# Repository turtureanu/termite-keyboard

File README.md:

# Termite

> [!IMPORTANT]
> **July 26th was the date I submitted this keyboard for review, today on October 6th I noticed that I forgot to add the firmware (which would have been caught by a reviewer).**

> [!IMPORTANT]
> Made for [Hackboard](https://hackpad.hackclub.com/keyboard), which requires having made a macropad as part of [Hackpad *V2*](https://hackpad.hackclub.com/). \
> Here is my Hackpad V2 macropad: [Wirepad](https://github.com/turtureanu/hackpad/tree/main/hackpads/wirepad)

This is a 34-key ortholinear split keyboard with built-in wrist supports, one 0.91" OLED display on each half, and low-profile mechanical Cherry-MX type switches (Gateron). I use a TRRS cable to connect the two halves. The case is 3D printed and uses 5 M2 screws (four M2x12, one M2x4).

For the firmware I'm using KMK.

I created this keyboard as a replacement for my laptop's keyboard, which might fail soon. I wanted an ortholinear split keyboard with fewer keys that would fit the Engram keyboard layout. In the past I designed a similar keyboard with an 0.42" OLED display under each key (inspired by [PolyKybd Split 72](https://github.com/thpoll83/PolyKybd)), but I lost that design due to an accidental mass file deletion that BTRFS couldn't recover.

## Schematics

| Main Schematic                                    |
| ------------------------------------------------- |
|  |

| Left LEDs                                                          | Right LEDs                                                           |
| ------------------------------------------------------------------ | -------------------------------------------------------------------- |
|  |  |

| Left Switches                                                              | Right Switches                                                               |
| -------------------------------------------------------------------------- | ---------------------------------------------------------------------------- |
|  |  |

## PCB

> The gerber files can be found in `pcb/gerber`

## BOM

| Name                                                                                                   | Sourcing   | Category  | Amount             | Price (total including shipping) |
|--------------------------------------------------------------------------------------------------------|------------|-----------|--------------------|----------------------------------|
| Orpheus Pico                                                                                           | Hack Club  | MCU       | 2                  | $0                               |
| [Gateron Low Profile Switch 2.0 Red](https://www.aliexpress.com/item/1005005385675189.html)            | AliExpress | switches  | 35 (set)           | $15.85                           |
| [Transparent Keycaps with Black Bed](https://www.aliexpress.com/item/1005005984548224.html)            | AliExpress | keycaps   | 40 (4x 10 pcs set) | $17.55                           |
| [SK6812 MINI-E LED](https://www.aliexpress.com/item/1005003056797785.html)                             | AliExpress | misc      | 100 (set)          | $5.13                            |
| [0.91" White OLED Display](https://www.aliexpress.com/item/1005001572699049.html)                      | AliExpress | misc      | 2                  | $3.61                            |
| [1N4148 THT Diode](https://www.aliexpress.com/item/4000142272546.html)                                 | AliExpress | misc      | 100 (set)          | $1.98                            |
| [PJ-320A 3.5mm Female Jack Connector](https://www.aliexpress.com/item/4001161286315.html)              | AliExpress | misc      | 20 (set)           | $2.13                            |
| [M2x4 Hexagon Countersunk Head Screw with Nut](https://www.aliexpress.com/item/1005006883320887.html)  | AliExpress | fasteners | 50 (set)           | $1.75                            |
| [M2x12 Hexagon Countersunk Head Screw with Nut](https://www.aliexpress.com/item/1005006883320887.html) | AliExpress | fasteners | 50 (set)           | $2.46                            |

Switches & keycaps:

- switches: $0.452 per switch
- keycaps: $0.438 per keycap

Fasteners: $4.21 total

Misc:

- LEDs: $0.0513 per LED
- OLED displays: $1.805 per OLED display
- 1N4148 Diodes: 0.0198 per diode
- Jack connector: $0.1065 per jack connector

Misc total: $12.85

JLCPCB cost, if I were to order it myself: $30.04 total (for the entire keyboard, i.e. both halves)

## Credits

- Raspberry Pi Pico model (RPi_Pico_SMD_TH.kicad_mod): https://github.com/ncarandini/KiCad-RP-Pico/
- SK6812-MINI-E (modified): https://github.com/keebio/Keebio-Parts.pretty
- Gateron Switch (SW_Gateron_LowProfile_THT.kicad_mod / modified): https://github.com/siderakb/key-switches.pretty.git
- 0.91 OLED display: https://github.com/gorbachev/KiCad-SSD1306-0.91-OLED-4pin-128x32.pretty/blob/master/SSD1306-0.91-OLED-4pin-128x32.kicad_mod
- Diode (D_DO-35_SOD27_P7.62mm_Horizontal.kicad_mod / modified): https://gitlab.com/kicad/libraries/kicad-footprints/
- PJ-320A 3.5mm 4-pin Jack Connector: https://github.com/nathanhborger/PJ-320A_KiCad_Library
- TRRS-PJ-320A footprint: https://gitlab.com/kicad/libraries/kicad-footprints/

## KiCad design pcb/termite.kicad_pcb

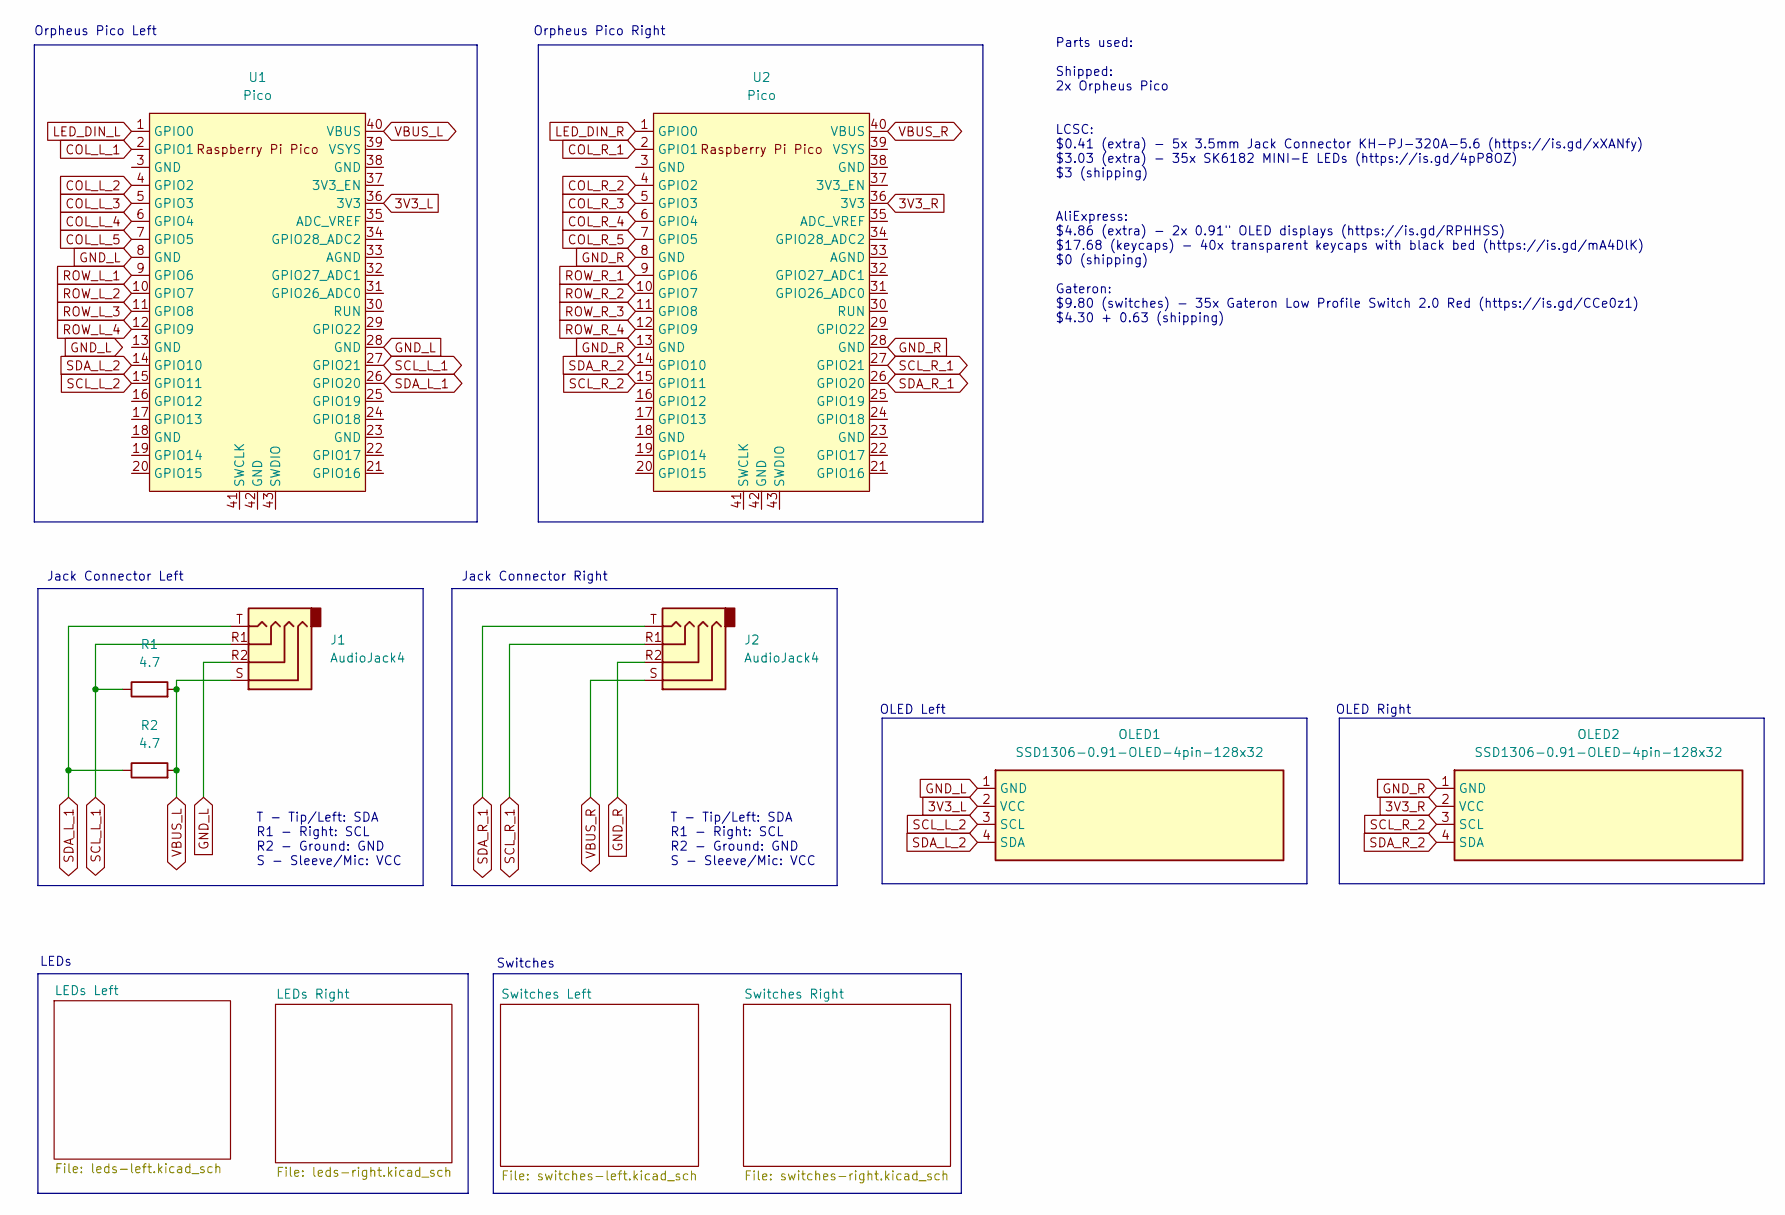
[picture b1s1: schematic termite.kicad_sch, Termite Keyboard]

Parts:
J1, J2: AudioJack4; TRRS-PJ-320A
OLED1, OLED2: SSD1306-0.91-OLED-4pin-128x32
R1, R2: 4.7; R_Axial_DIN0204_L3.6mm_D1.6mm_P5.08mm_Horizontal
U1, U2: Pico; RPi_Pico_SMD_TH

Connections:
3V3_L: OLED1.2 (VCC), U1.36 (3V3)
3V3_R: OLED2.2 (VCC), U2.36 (3V3)
COL_L_1: U1.2 (GPIO1); also elsewhere on the board
COL_L_2: U1.4 (GPIO2); also elsewhere on the board
COL_L_3: U1.5 (GPIO3); also elsewhere on the board
COL_L_4: U1.6 (GPIO4); also elsewhere on the board
COL_L_5: U1.7 (GPIO5); also elsewhere on the board
COL_R_1: U2.2 (GPIO1); also elsewhere on the board
COL_R_2: U2.4 (GPIO2); also elsewhere on the board
COL_R_3: U2.5 (GPIO3); also elsewhere on the board
COL_R_4: U2.6 (GPIO4); also elsewhere on the board
COL_R_5: U2.7 (GPIO5); also elsewhere on the board
GND_L: J1.R2, OLED1.1 (GND), U1.8 (GND), U1.28 (GND); also elsewhere on the board
GND_R: J2.R2, OLED2.1 (GND), U2.8 (GND), U2.13 (GND), U2.28 (GND); also elsewhere on the board
LED_DIN_L: U1.1 (GPIO0); also elsewhere on the board
LED_DIN_R: U2.1 (GPIO0); also elsewhere on the board
ROW_L_1: U1.9 (GPIO6); also elsewhere on the board
ROW_L_2: U1.10 (GPIO7); also elsewhere on the board
ROW_L_3: U1.11 (GPIO8); also elsewhere on the board
ROW_L_4: U1.12 (GPIO9); also elsewhere on the board
ROW_R_1: U2.9 (GPIO6); also elsewhere on the board
ROW_R_2: U2.10 (GPIO7); also elsewhere on the board
ROW_R_3: U2.11 (GPIO8); also elsewhere on the board
ROW_R_4: U2.12 (GPIO9); also elsewhere on the board
SCL_L_1: J1.R1, R1.1, U1.27 (GPIO21)
SCL_L_2: OLED1.3 (SCL), U1.15 (GPIO11)
SCL_R_1: J2.R1, U2.27 (GPIO21)
SCL_R_2: OLED2.3 (SCL), U2.15 (GPIO11)
SDA_L_1: J1.T, R2.1, U1.26 (GPIO20)
SDA_L_2: OLED1.4 (SDA), U1.14 (GPIO10)
SDA_R_1: J2.T, U2.26 (GPIO20)
SDA_R_2: OLED2.4 (SDA), U2.14 (GPIO10)
VBUS_L: J1.S, R1.2, R2.2, U1.40 (VBUS); also elsewhere on the board
VBUS_R: J2.S, U2.40 (VBUS); also elsewhere on the board

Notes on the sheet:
OLED Right
LEDs
T - Tip/Left: SDA R1 - Right: SCL R2 - Ground: GND S - Sleeve/Mic: VCC
Jack Connector Right
Orpheus Pico Right
OLED Left
Parts used: Shipped: 2x Orpheus Pico LCSC: $0.41 (extra) - 5x 3.5mm Jack Connector KH-PJ-320A-5.6 (https://is.gd/xXANfy) $3.03 (extra) - 35x SK6182 MINI-E LEDs (https://is.gd/4pP8OZ) $3 (shipping) AliExpress: $4.86 (extra) - 2x 0.91" OLED displays (https://is.gd/RPHHSS) $17.68 (keycaps) - 40x trans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
Jack Connector Left
Switches
Orpheus Pico Left

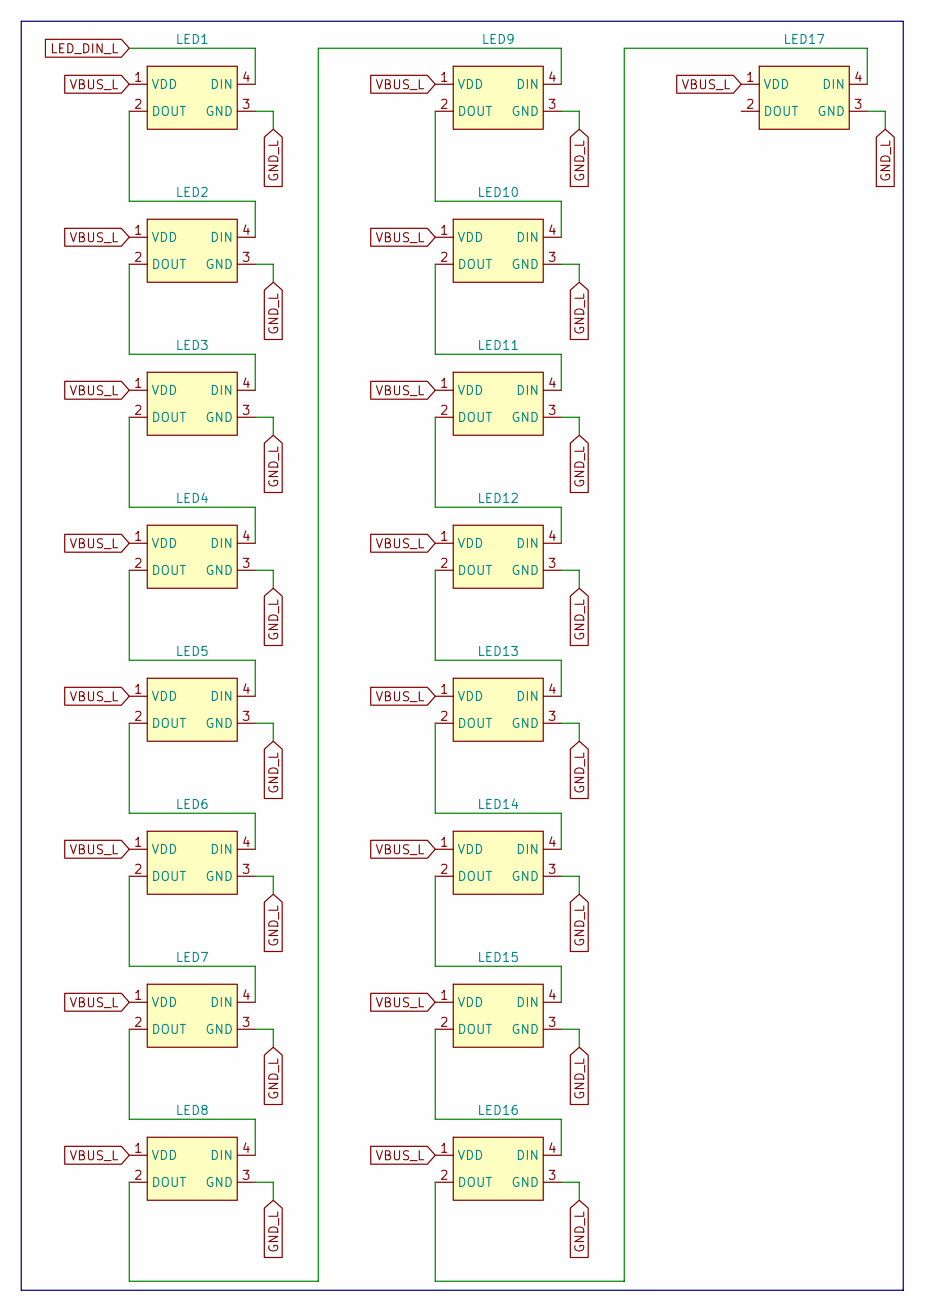
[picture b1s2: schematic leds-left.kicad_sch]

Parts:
LED1, LED2, LED3, LED4, LED5, LED6, LED7, LED8, LED9, LED10, LED11, LED12, LED13, LED14, LED15, LED16, LED17: SK6812-MINI-E

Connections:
GND_L: LED1.3 (GND), LED2.3 (GND), LED3.3 (GND), LED4.3 (GND), LED5.3 (GND), LED6.3 (GND), LED7.3 (GND), LED8.3 (GND), LED9.3 (GND), LED10.3 (GND), LED11.3 (GND), LED12.3 (GND), LED13.3 (GND), LED14.3 (GND), LED15.3 (GND), LED16.3 (GND), LED17.3 (GND); also elsewhere on the board
LED_DIN_L: LED1.4 (DIN); also elsewhere on the board
unnamed: LED1.2 (DOUT), LED2.4 (DIN)
unnamed: LED2.2 (DOUT), LED3.4 (DIN)
unnamed: LED3.2 (DOUT), LED4.4 (DIN)
unnamed: LED4.2 (DOUT), LED5.4 (DIN)
unnamed: LED5.2 (DOUT), LED6.4 (DIN)
unnamed: LED6.2 (DOUT), LED7.4 (DIN)
unnamed: LED7.2 (DOUT), LED8.4 (DIN)
unnamed: LED8.2 (DOUT), LED9.4 (DIN)
unnamed: LED9.2 (DOUT), LED10.4 (DIN)
unnamed: LED10.2 (DOUT), LED11.4 (DIN)
unnamed: LED11.2 (DOUT), LED12.4 (DIN)
unnamed: LED12.2 (DOUT), LED13.4 (DIN)
unnamed: LED13.2 (DOUT), LED14.4 (DIN)
unnamed: LED14.2 (DOUT), LED15.4 (DIN)
unnamed: LED15.2 (DOUT), LED16.4 (DIN)
unnamed: LED16.2 (DOUT), LED17.4 (DIN)
VBUS_L: LED1.1 (VDD), LED2.1 (VDD), LED3.1 (VDD), LED4.1 (VDD), LED5.1 (VDD), LED6.1 (VDD), LED7.1 (VDD), LED8.1 (VDD), LED9.1 (VDD), LED10.1 (VDD), LED11.1 (VDD), LED12.1 (VDD), LED13.1 (VDD), LED14.1 (VDD), LED15.1 (VDD), LED16.1 (VDD), LED17.1 (VDD); also elsewhere on the board

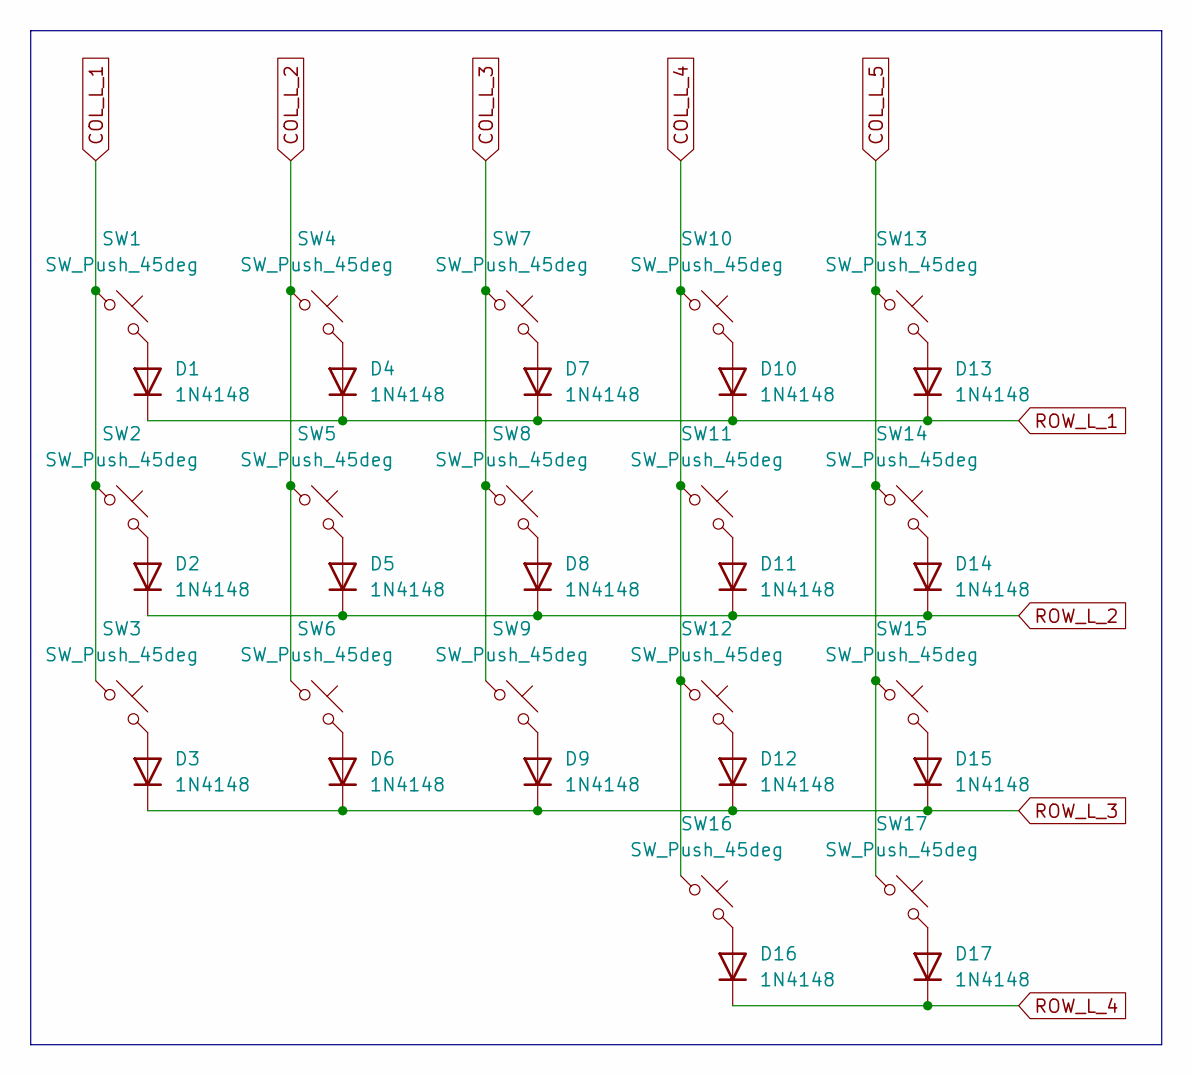
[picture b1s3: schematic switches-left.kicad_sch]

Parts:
D1, D2, D3, D4, D5, D6, D7, D8, D9, D10, D11, D12, D13, D14, D15, D16, D17: 1N4148; D_DO-35_SOD27_P7.62mm_Horizontal
SW1, SW2, SW3, SW4, SW5, SW6, SW7, SW8, SW9, SW10, SW11, SW12, SW13, SW14, SW15, SW16, SW17: SW_Push_45deg; SW_Gateron_LowProfile_THT

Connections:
COL_L_1: SW1.1, SW2.1, SW3.1; also elsewhere on the board
COL_L_2: SW4.1, SW5.1, SW6.1; also elsewhere on the board
COL_L_3: SW7.1, SW8.1, SW9.1; also elsewhere on the board
COL_L_4: SW10.1, SW11.1, SW12.1, SW16.1; also elsewhere on the board
COL_L_5: SW13.1, SW14.1, SW15.1, SW17.1; also elsewhere on the board
unnamed: D1.2 (A), SW1.2
unnamed: D2.2 (A), SW2.2
unnamed: D3.2 (A), SW3.2
unnamed: D4.2 (A), SW4.2
unnamed: D5.2 (A), SW5.2
unnamed: D6.2 (A), SW6.2
unnamed: D7.2 (A), SW7.2
unnamed: D8.2 (A), SW8.2
unnamed: D9.2 (A), SW9.2
unnamed: D10.2 (A), SW10.2
unnamed: D11.2 (A), SW11.2
unnamed: D12.2 (A), SW12.2
unnamed: D13.2 (A), SW13.2
unnamed: D14.2 (A), SW14.2
unnamed: D15.2 (A), SW15.2
unnamed: D16.2 (A), SW16.2
unnamed: D17.2 (A), SW17.2
ROW_L_1: D1.1 (K), D4.1 (K), D7.1 (K), D10.1 (K), D13.1 (K); also elsewhere on the board
ROW_L_2: D2.1 (K), D5.1 (K), D8.1 (K), D11.1 (K), D14.1 (K); also elsewhere on the board
ROW_L_3: D3.1 (K), D6.1 (K), D9.1 (K), D12.1 (K), D15.1 (K); also elsewhere on the board
ROW_L_4: D16.1 (K), D17.1 (K); also elsewhere on the board

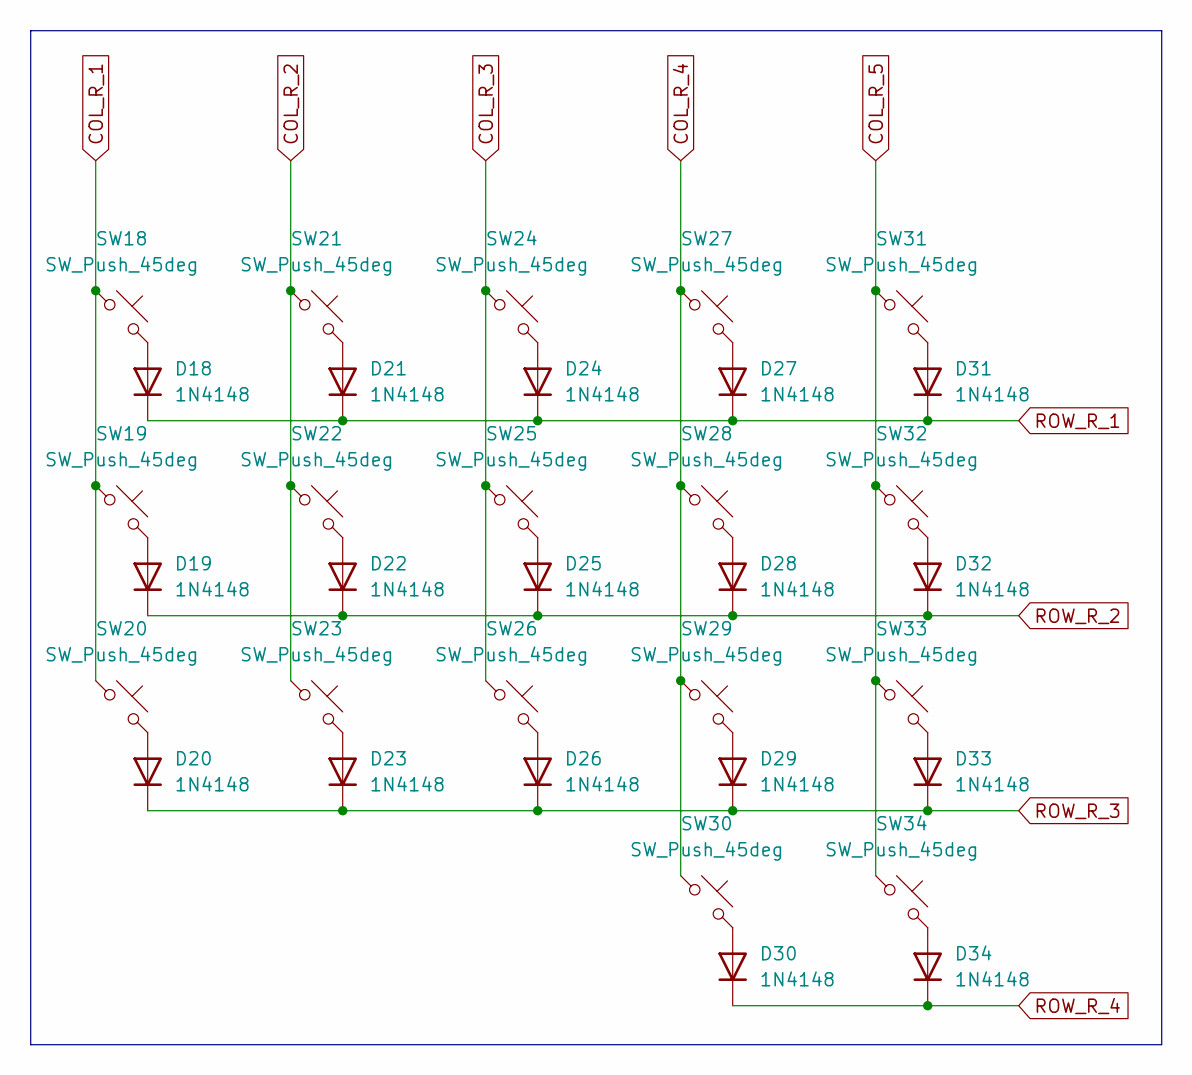
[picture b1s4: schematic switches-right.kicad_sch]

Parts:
D18, D19, D20, D21, D22, D23, D24, D25, D26, D27, D28, D29, D30, D31, D32, D33, D34: 1N4148; D_DO-35_SOD27_P7.62mm_Horizontal
SW18, SW19, SW20, SW21, SW22, SW23, SW24, SW25, SW26, SW27, SW28, SW29, SW30, SW31, SW32, SW33, SW34: SW_Push_45deg; SW_Gateron_LowProfile_THT

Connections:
COL_R_1: SW18.1, SW19.1, SW20.1; also elsewhere on the board
COL_R_2: SW21.1, SW22.1, SW23.1; also elsewhere on the board
COL_R_3: SW24.1, SW25.1, SW26.1; also elsewhere on the board
COL_R_4: SW27.1, SW28.1, SW29.1, SW30.1; also elsewhere on the board
COL_R_5: SW31.1, SW32.1, SW33.1, SW34.1; also elsewhere on the board
unnamed: D18.2 (A), SW18.2
unnamed: D19.2 (A), SW19.2
unnamed: D20.2 (A), SW20.2
unnamed: D21.2 (A), SW21.2
unnamed: D22.2 (A), SW22.2
unnamed: D23.2 (A), SW23.2
unnamed: D24.2 (A), SW24.2
unnamed: D25.2 (A), SW25.2
unnamed: D26.2 (A), SW26.2
unnamed: D27.2 (A), SW27.2
unnamed: D28.2 (A), SW28.2
unnamed: D29.2 (A), SW29.2
unnamed: D30.2 (A), SW30.2
unnamed: D31.2 (A), SW31.2
unnamed: D32.2 (A), SW32.2
unnamed: D33.2 (A), SW33.2
unnamed: D34.2 (A), SW34.2
ROW_R_1: D18.1 (K), D21.1 (K), D24.1 (K), D27.1 (K), D31.1 (K); also elsewhere on the board
ROW_R_2: D19.1 (K), D22.1 (K), D25.1 (K), D28.1 (K), D32.1 (K); also elsewhere on the board
ROW_R_3: D20.1 (K), D23.1 (K), D26.1 (K), D29.1 (K), D33.1 (K); also elsewhere on the board
ROW_R_4: D30.1 (K), D34.1 (K); also elsewhere on the board

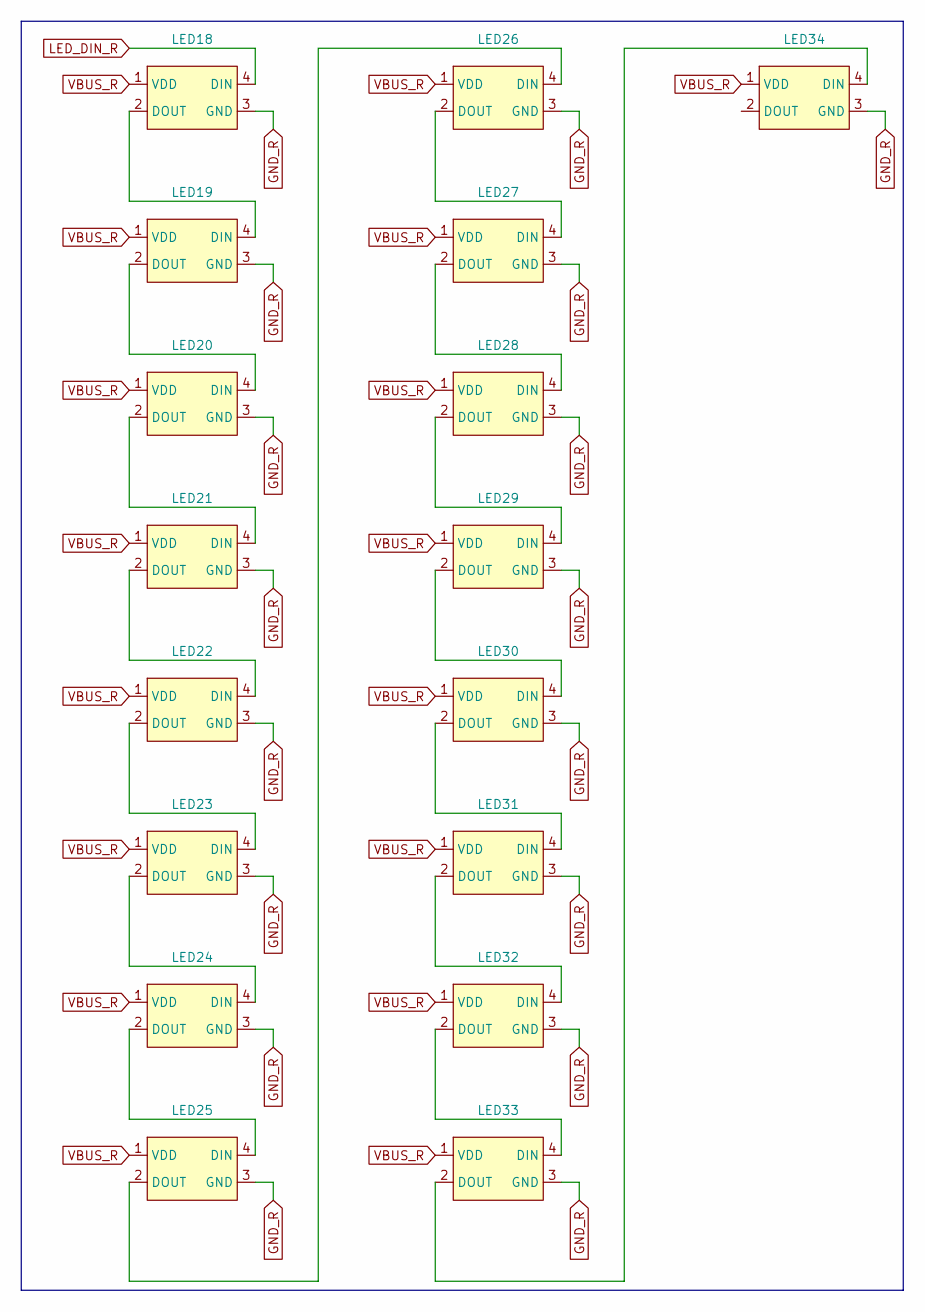
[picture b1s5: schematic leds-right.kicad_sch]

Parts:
LED18, LED19, LED20, LED21, LED22, LED23, LED24, LED25, LED26, LED27, LED28, LED29, LED30, LED31, LED32, LED33, LED34: SK6812-MINI-E

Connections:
GND_R: LED18.3 (GND), LED19.3 (GND), LED20.3 (GND), LED21.3 (GND), LED22.3 (GND), LED23.3 (GND), LED24.3 (GND), LED25.3 (GND), LED26.3 (GND), LED27.3 (GND), LED28.3 (GND), LED29.3 (GND), LED30.3 (GND), LED31.3 (GND), LED32.3 (GND), LED33.3 (GND), LED34.3 (GND); also elsewhere on the board
LED_DIN_R: LED18.4 (DIN); also elsewhere on the board
unnamed: LED18.2 (DOUT), LED19.4 (DIN)
unnamed: LED19.2 (DOUT), LED20.4 (DIN)
unnamed: LED20.2 (DOUT), LED21.4 (DIN)
unnamed: LED21.2 (DOUT), LED22.4 (DIN)
unnamed: LED22.2 (DOUT), LED23.4 (DIN)
unnamed: LED23.2 (DOUT), LED24.4 (DIN)
unnamed: LED24.2 (DOUT), LED25.4 (DIN)
unnamed: LED25.2 (DOUT), LED26.4 (DIN)
unnamed: LED26.2 (DOUT), LED27.4 (DIN)
unnamed: LED27.2 (DOUT), LED28.4 (DIN)
unnamed: LED28.2 (DOUT), LED29.4 (DIN)
unnamed: LED29.2 (DOUT), LED30.4 (DIN)
unnamed: LED30.2 (DOUT), LED31.4 (DIN)
unnamed: LED31.2 (DOUT), LED32.4 (DIN)
unnamed: LED32.2 (DOUT), LED33.4 (DIN)
unnamed: LED33.2 (DOUT), LED34.4 (DIN)
VBUS_R: LED18.1 (VDD), LED19.1 (VDD), LED20.1 (VDD), LED21.1 (VDD), LED22.1 (VDD), LED23.1 (VDD), LED24.1 (VDD), LED25.1 (VDD), LED26.1 (VDD), LED27.1 (VDD), LED28.1 (VDD), LED29.1 (VDD), LED30.1 (VDD), LED31.1 (VDD), LED32.1 (VDD), LED33.1 (VDD), LED34.1 (VDD); also elsewhere on the board

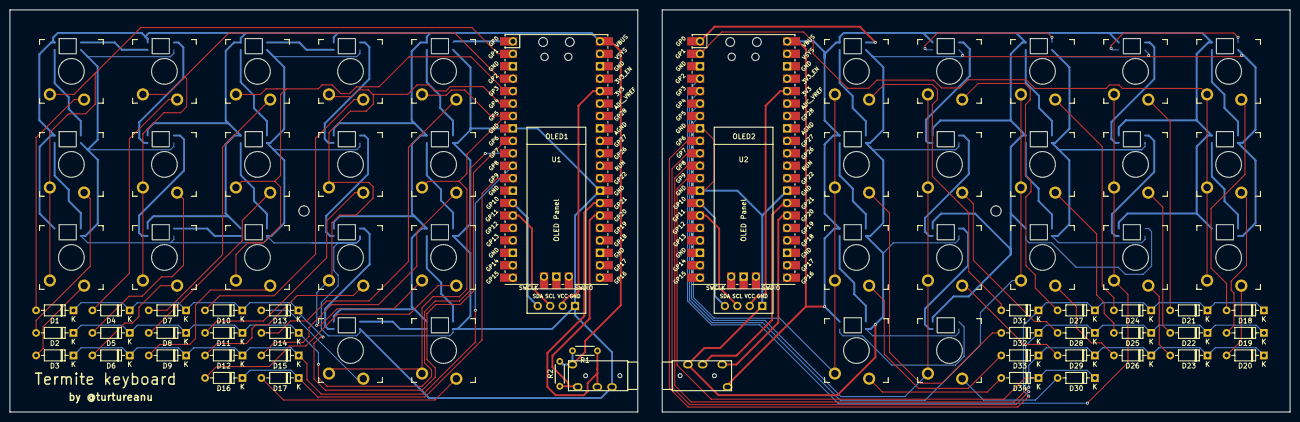
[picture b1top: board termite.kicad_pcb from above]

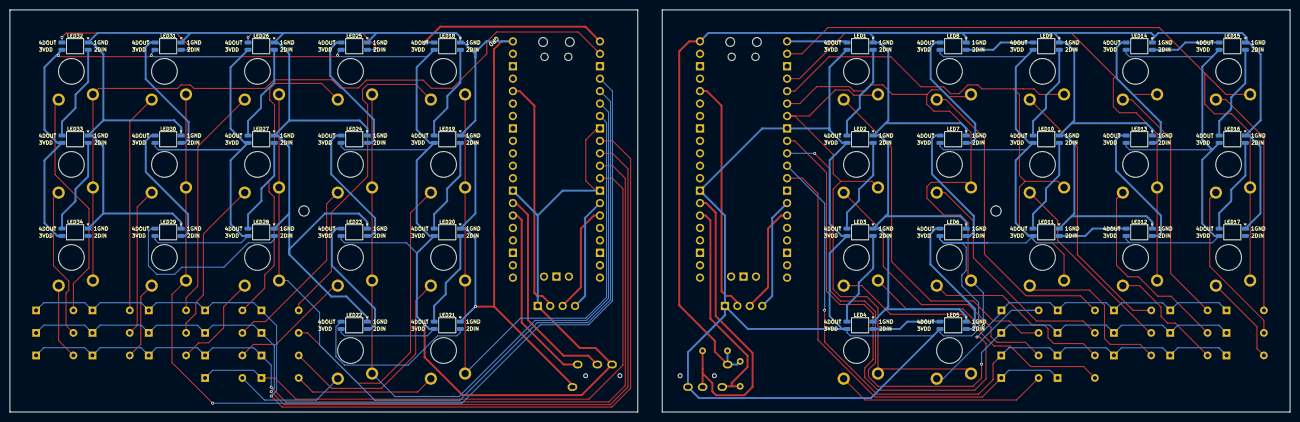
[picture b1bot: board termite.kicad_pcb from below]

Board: 2 copper layers, 261.3 x 82.0 mm, 110 parts (34 on the bottom side), 100 nets.

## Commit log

2025-04-05 add: project files (dirty)
2025-06-21 fix: bring jack connectors to the edge
2025-07-23 feat: finish case + reorganize project structure
2025-07-23 ignore: termite backups
2025-07-26 add: description, screenshots, BOM
2025-07-26 add: important note about Hackpad
2025-07-26 add: gerber files for both halves
2025-07-26 add(README): note about JLCPCB order
2025-07-26 feat(README): mention the OLED displays in the short description
2025-10-06 FORGOT TO ADD THE FIRMWARE
2025-10-29 add: production directory
2025-12-10 fix: production directory file structure
2026-01-16 add: assembled keyboard step
2026-03-28 Add Left & Right half PCBs to BOM
